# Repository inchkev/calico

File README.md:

# calico

calico is a 54 key (6x4+3 split) column-staggered choc-spaced split ergonomic keyboard with freehanded traces and diode sprinkles

* pro micro based
* reversible pcb
* choc v1 hotswap only

## board

### v0.2

changes from v0.1

* brought trrs jack all the way to the edge
* brought pro micro down a bit, close gap with trrs
* modify footprints for reset and trrs
* use different footprint for the pro micro

## to build calico, you'll need:

* 2x calico v0.2 pcbs
* 2x pro micro compatible boards
* 54x choc v1 switches
* 54x choc 1u keycaps (I used MBK profile)
* 54x Kailh choc hotswap sockets
* 54x SOD-123 diodes (I used 1N4148W)
* 2x TRRS PJ-320A jacks
* 1x TRRS cable
* 2x tact switch (optional, just carry a paperclip)
* at least 8x rubber feet (I used 10)
* 1x usb-c cable

I'd also recommend socketing your pro micros:

* 4x BBL-112-T-E Samtec ([mouser](https://www.mouser.com/ProductDetail/Samtec/BBL-112-T-E?qs=FESYatJ8odKicQFiFw2tKA%3D%3D), [digikey](https://www.digikey.com/en/products/detail/samtec-inc/BBL-112-T-E/1099406))
* 4x 315-43-112-41-003000 Mill-Max ([mouser](https://www.mouser.com/ProductDetail/Mill-Max/315-43-112-41-003000?qs=s8Nb1z4Wn%2FRfWrVqQ0TOuQ%3D%3D), [digikey](https://www.digikey.com/en/products/detail/mill-max-manufacturing-corp/315-43-112-41-003000/4455232))

## calico was inspired by

* [Lily58 by kata0510](https://github.com/kata0510/Lily58)
* [Peter Blasser's Ciat-Lonbarde PCBs](https://www.ciat-lonbarde.net/)
* [bugs by jimmerricks](https://github.com/jimmerricks/bugs)
* [Swoop MX by jimmerricks](https://github.com/jimmerricks/swoop)
* [Sweep Half Swept by David Barr](https://github.com/davidphilipbarr/Sweep)
* [keyboards by mindhatch](https://github.com/mindhatch/keyboards)
* [Sofle by Joseph Adamčík](https://josefadamcik.github.io/SofleKeyboard/)
* [TOTEM by GEIGEIGEIST](https://github.com/GEIGEIGEIST/TOTEM)

### and designed with the use of

* [ergogen](https://github.com/ergogen/ergogen)
* [kicad-kbplacer](https://github.com/adamws/kicad-kbplacer/tree/master)

### and licensed under

[CERN-OHL-W-2.0](https://spdx.org/licenses/CERN-OHL-W-2.0.html) overall. calico uses footprints, modified and unmodified, under different licenses. see [ATTRIBUTIONS.md](ATTRIBUTIONS.md).

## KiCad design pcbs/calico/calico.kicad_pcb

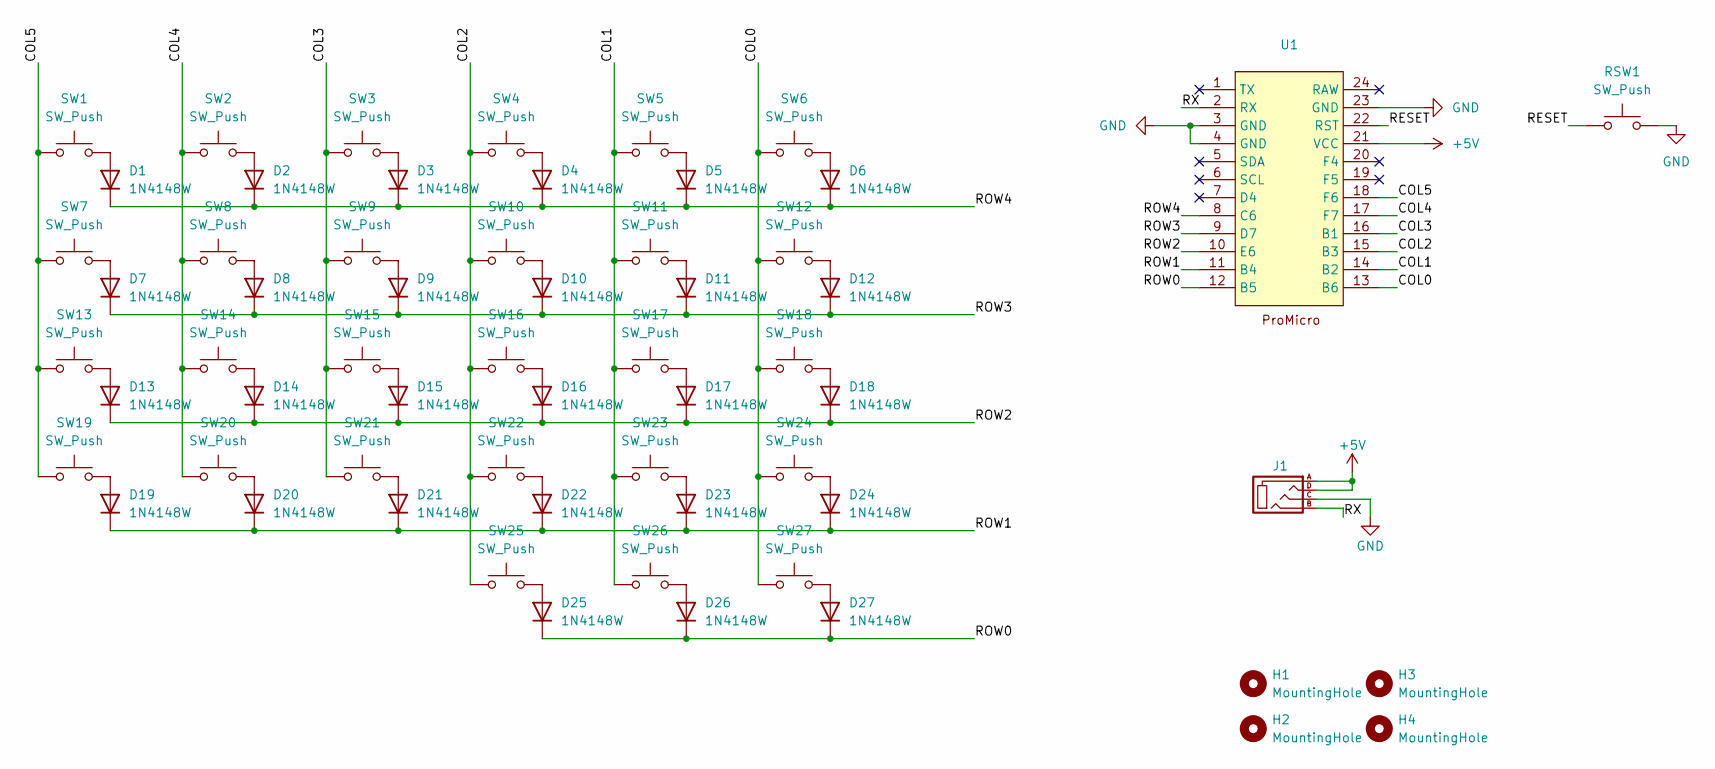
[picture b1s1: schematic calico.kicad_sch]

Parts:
D1, D2, D3, D4, D5, D6, D7, D8, D9, D10, D11, D12, D13, D14, D15, D16, D17, D18, D19, D20, D21, D22, D23, D24, D25, D26, D27: 1N4148W; D3_SMD_modified
H1, H2, H3, H4: MountingHole; MountingHole_2.2mm_M2_ISO7380_Pad_TopBottom
J1: MJ-4PP-9-kbd-corne-light-rescue; TRRS-3pin_modified
RSW1: SW_Push; Reset_modified
SW1, SW2, SW3, SW4, SW5, SW6, SW7, SW8, SW9, SW10, SW11, SW12, SW13, SW14, SW15, SW16, SW17, SW18, SW19, SW20, SW21, SW22, SW23, SW24, SW25, SW26, SW27: SW_Push; Kailh_socket_PG1350_reversible
U1: ProMicro_jumpers

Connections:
+5V: J1.A, J1.D, U1.21 (VCC)
/COL0: SW6.1, SW12.1, SW18.1, SW24.1, SW27.1, U1.13 (B6)
/COL1: SW5.1, SW11.1, SW17.1, SW23.1, SW26.1, U1.14 (B2)
/COL2: SW4.1, SW10.1, SW16.1, SW22.1, SW25.1, U1.15 (B3)
/COL3: SW3.1, SW9.1, SW15.1, SW21.1, U1.16 (B1)
/COL4: SW2.1, SW8.1, SW14.1, SW20.1, U1.17 (F7)
/COL5: SW1.1, SW7.1, SW13.1, SW19.1, U1.18 (F6)
/RESET: RSW1.1, U1.22 (RST)
/ROW0: D25.1 (K), D26.1 (K), D27.1 (K), U1.12 (B5)
/ROW1: D19.1 (K), D20.1 (K), D21.1 (K), D22.1 (K), D23.1 (K), D24.1 (K), U1.11 (B4)
/ROW2: D13.1 (K), D14.1 (K), D15.1 (K), D16.1 (K), D17.1 (K), D18.1 (K), U1.10 (E6)
/ROW3: D7.1 (K), D8.1 (K), D9.1 (K), D10.1 (K), D11.1 (K), D12.1 (K), U1.9 (D7)
/ROW4: D1.1 (K), D2.1 (K), D3.1 (K), D4.1 (K), D5.1 (K), D6.1 (K), U1.8 (C6)
/RX: J1.B, U1.2 (RX)
GND: J1.C, RSW1.2, U1.3 (GND), U1.4 (GND), U1.23 (GND)
unnamed: D1.2 (A), SW1.2
unnamed: D2.2 (A), SW2.2
unnamed: D3.2 (A), SW3.2
unnamed: D4.2 (A), SW4.2
unnamed: D5.2 (A), SW5.2
unnamed: D6.2 (A), SW6.2
unnamed: D7.2 (A), SW7.2
unnamed: D8.2 (A), SW8.2
unnamed: D9.2 (A), SW9.2
unnamed: D10.2 (A), SW10.2
unnamed: D11.2 (A), SW11.2
unnamed: D12.2 (A), SW12.2
unnamed: D13.2 (A), SW13.2
unnamed: D14.2 (A), SW14.2
unnamed: D15.2 (A), SW15.2
unnamed: D16.2 (A), SW16.2
unnamed: D17.2 (A), SW17.2
unnamed: D18.2 (A), SW18.2
unnamed: D19.2 (A), SW19.2
unnamed: D20.2 (A), SW20.2
unnamed: D21.2 (A), SW21.2
unnamed: D22.2 (A), SW22.2
unnamed: D23.2 (A), SW23.2
unnamed: D24.2 (A), SW24.2
unnamed: D25.2 (A), SW25.2
unnamed: D26.2 (A), SW26.2
unnamed: D27.2 (A), SW27.2

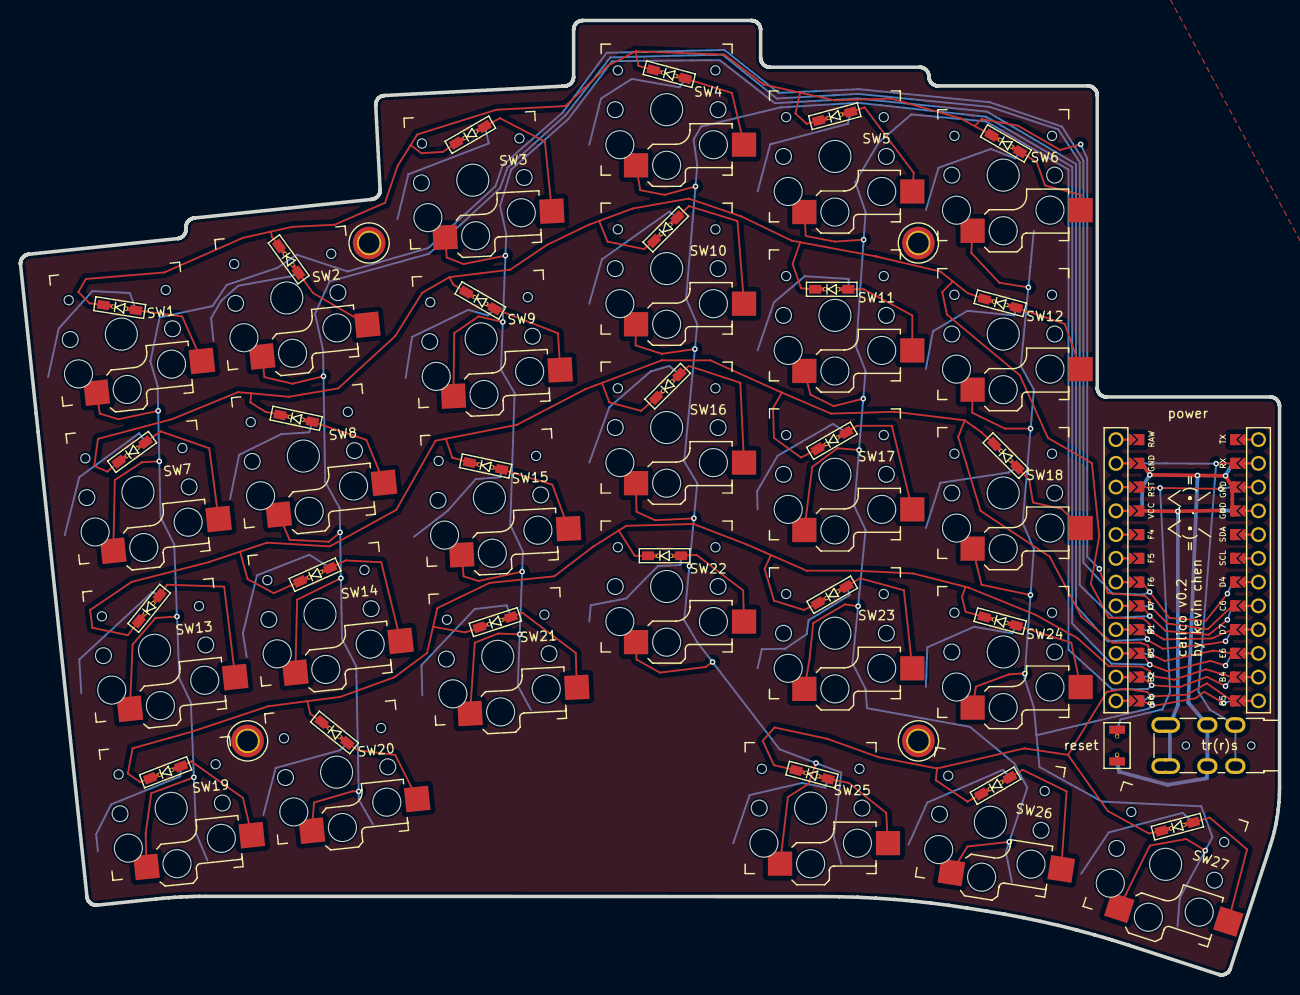
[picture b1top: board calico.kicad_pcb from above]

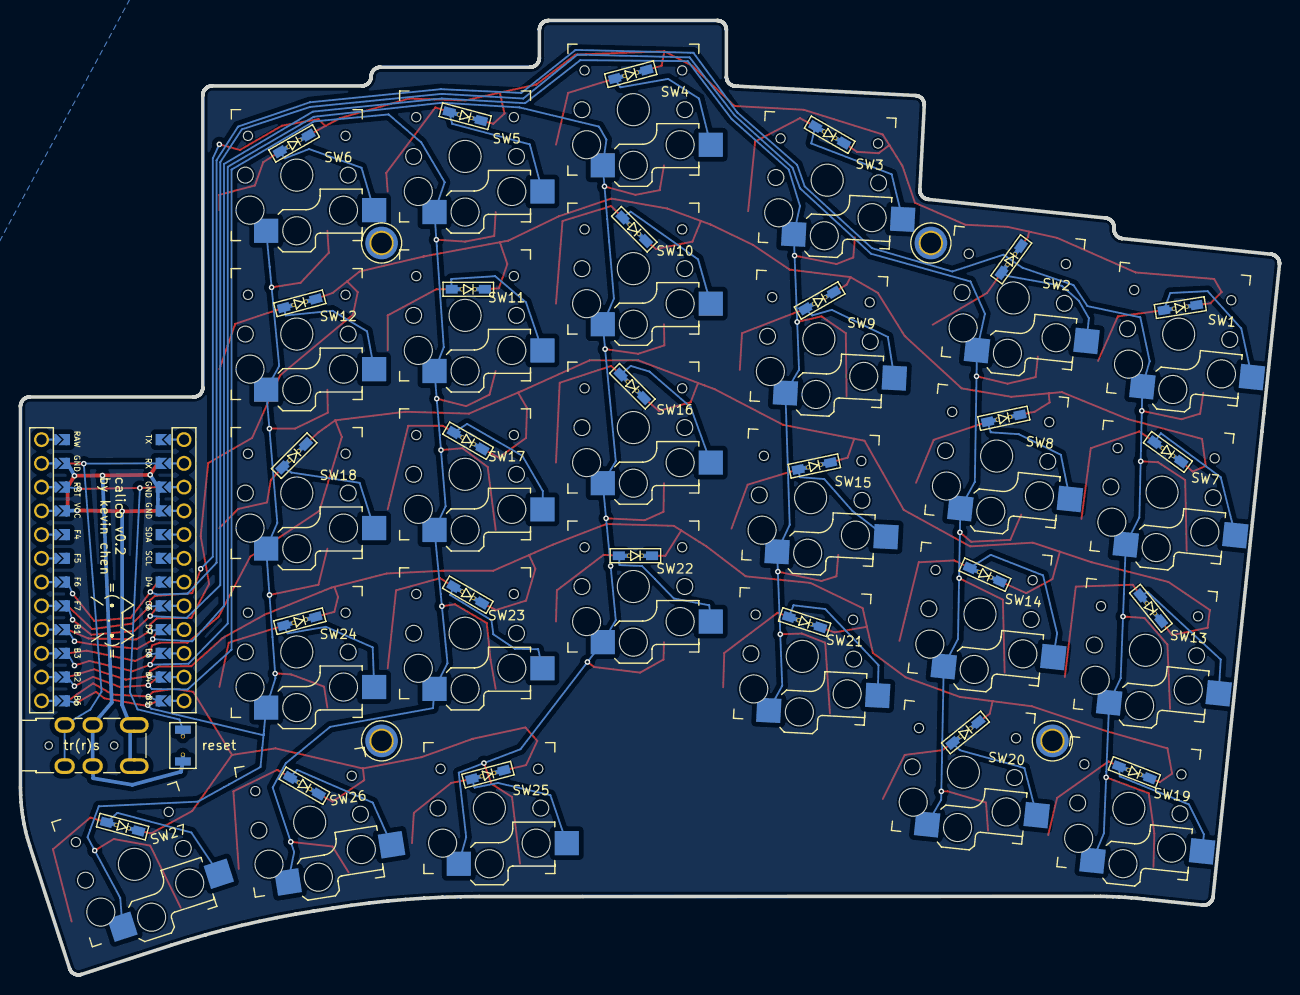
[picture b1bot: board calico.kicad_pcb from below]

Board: 2 copper layers, 134.7 x 102.1 mm, 61 parts (27 on the bottom side), 42 nets.

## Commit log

2024-12-10 meow
2024-12-11 more
2024-12-11 attributions
2024-12-19 v0.2 initial
2024-12-21 v0.2 updated
2024-12-23 add license
2024-12-24 Add licenses
2024-12-31 polish
2024-12-31 edit trace color
2024-12-31 better cover shot
2025-01-01 edit readme
